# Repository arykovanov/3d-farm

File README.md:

Introduction
------------

This is an application for testing differen Edge AI, Tiny ML models.

Memory note
-----------

By default most of the memory is reserved for LUA bindings. But ML models
require much memory and it is required to balance between differen parts.

ESP32s3 can have 8MB or 16MB. 
XEdge32 reserves memory of itself in the mainServerTask function by allocating aditional space in BSS section. 
```
#ifdef USE_DLMALLOC
   /* Allocate as much pSRAM as possible */
#if CONFIG_IDF_TARGET_ESP32S3
   EXT_RAM_BSS_ATTR static char poolBuf[3*1024*1024 + 5*1024];
#else
   EXT_RAM_BSS_ATTR static char poolBuf[7*1024*1024 + 5*1024];
#endif
   init_dlmalloc(poolBuf, poolBuf + sizeof(poolBuf));
#else
   #error must use dlmalloc
#endif
```

Because of this available size of free PSRAM memory pool can be allocated too small for ML application.
You will see such ESP32 boot logs:

```
I (504) esp_psram: Found 8MB PSRAM device
I (1030) esp_psram: Adding pool of 1092K of PSRAM memory to heap allocator
```

In the log output above you can see ~1MB of free memory for third party libraries.
Image recognition models might require 1.5-3-7MB of memory and thus image recognition can fail with memory errors.

Impulse Edge EON
----------------

This ESP32 project can run model from project https://studio.edgeimpulse.com/public/790245/live

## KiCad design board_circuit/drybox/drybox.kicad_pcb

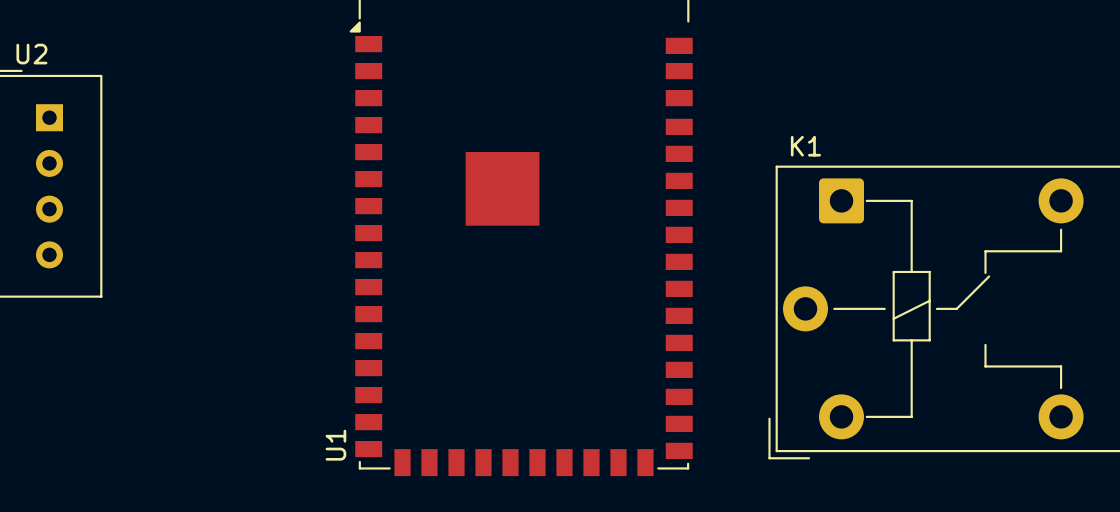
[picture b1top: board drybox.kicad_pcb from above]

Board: 2 copper layers, 3 parts (0 on the bottom side), 4 nets, no tracks yet.

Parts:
K1: JQC-3FF-005-1Z; Relay_SPDT_Hongfa_JQC-3FF_0XX-1Z
U1: ESP32-S2-WROVER
U2: DHT11; Aosong_DHT11_5.5x12.0_P2.54mm

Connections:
GNDREF: K1.A2, U1.1 (GND), U1.26 (GND), U1.42 (GND), U1.43 (GND), U2.4 (GND)
unnamed: U1.2 (3V3), U2.1 (VDD)
unnamed: U1.4 (IO01), U2.2 (DATA)
unnamed: K1.A1, U1.5 (IO02)

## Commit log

2025-10-08 Initial commit recognition works with impulse edge: added a lua function that runs classification
2025-10-08 More logs about memory
2025-10-08 Addres models README with summaries about ML frameforks
2025-10-08 Added README with project description
2026-04-03 Added lsp_apps: mock_sso, login, humidity_control
2026-04-03 Added kickad circuit
2026-04-03 Added freecad models
2026-04-03 Deleted managed_components
2026-04-03 Updated main files
2026-04-03 Updated Xedge sources
2026-04-03 Move ESP32 firmware to xedge folder
2026-04-03 Renamed folder server to apps
2026-04-04 Added simulator application of DHT11 sensor and GPIO port
2026-04-04 Fixed mock_sso workflow: it shows login form
2026-04-04 Login workflow works with mock_sso
